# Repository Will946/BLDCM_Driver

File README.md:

# BLDC Motor Controller

> [!NOTE]
> This project is currently in active development. Features and documentation are subject to change.

## Table of Contents
- [Project Overview](#project-overview)
- [Electronics](#electronics)
  - [MCU PCB (Top Board)](#mcu-pcb-top-board)
  - [Power PCB (Bottom Board)](#power-pcb-bottom-board)
  - [Complete Stack-Up](#complete-stack-up)
- [Results](#results)

---

## Project Overview

This project aims to develop a **high-precision Brushless DC (BLDC) motor controller** from scratch, covering both hardware and firmware aspects. The controller is designed for advanced motor control applications, leveraging a powerful STM32 microcontroller, a dedicated motor driver IC, and comprehensive sensing capabilities for precise operation and rotor position estimation.

The core of the system is a custom two-board stack: an MCU board housing the main control logic and a power board managing motor drive and sensing. The two boards connect through a Molex board-to-board stack connector, keeping the whole assembly compact enough to sit directly behind the motor.

<div align="center">
  
  &nbsp;&nbsp;
  
</div>

---

## Electronics

The electronics consist of two interconnected custom-designed Printed Circuit Boards (PCBs), designed using **KiCad**. Both boards are **4-layer, circular designs** sized to fit inside the motor housing, and stack together through a **Molex board-to-board connector** that carries power, control signals, and communication lines between them.

### MCU PCB (Top Board)

The top PCB is the brain of the controller. It runs the control loop, reads all of the position/motion sensors, and exposes the debug and status interfaces a developer needs while bringing the system up.

<div align="center">
  
  &nbsp;&nbsp;
  
</div>

**How it works:**
- The **STM32F4 microcontroller** sits at the center of the board and runs the motor control algorithm (trapezoidal or FOC) in a fast timer-driven loop, reading sensor data and updating the PWM duty cycles sent down to the power board on every cycle.
- The **AS5048A** magnetic angle encoder reads the rotor's absolute position with 14-bit resolution off a magnet mounted on the motor shaft. This gives the controller true rotor position for commutation, rather than relying on back-EMF sensing, which matters a lot at low speed and standstill.
- The **ISM330DHCX IMU** adds acceleration and angular velocity data from the board itself, which is useful for detecting external motion or vibration and for any application where the motor's own orientation/movement (not just the rotor's) needs to be tracked.
- An **SK6805 RGB LED ring** wraps around the board's edge and is driven per-LED to show system status (idle, running, fault, etc.) at a glance without needing a debugger attached.
- A **reset button** is broken out on the edge for quick resets during bring-up and testing.
- The top-side connector routes down to the power board through the Molex stack connector, carrying the PWM/gate signals, sensor feedback, and shared power rails between the two boards.

### Power PCB (Bottom Board)

The bottom PCB handles everything high-current: driving the motor phases, sensing voltage and current, and providing the external connectivity for power and communication.

<div align="center">
  
  &nbsp;&nbsp;
  
</div>

**How it works:**
- The **TMC6300** is a fully integrated 3-phase gate driver/MOSFET bridge. It takes the PWM commutation signals from the MCU board and switches the three motor phases directly — there's no separate discrete MOSFET stage, which keeps the board small enough to fit the round form factor.
- Three **INA240** current sense amplifiers measure the current on each motor phase in real time. This phase current feedback is what the FOC algorithm on the MCU board needs to run its current control loops (the Park/Clarke transforms depend on accurate, low-noise current readings).
- Four voltage sensing networks monitor the **DC bus voltage** plus all **three phase voltages** (after filtering), letting the firmware detect undervoltage/overvoltage conditions and, combined with the current sensing, estimate power delivered to the motor.
- The **TCAN1462** CAN FD transceiver lets multiple motor controllers be **daisy-chained together on a single CAN bus**, so a single host can address and command several motors (e.g. in a multi-joint robot) over one pair of wires.
- A **J-Link 14-pin SWD connector** breaks out the STM32's debug port for flashing and live debugging with a J-Link probe.
- A **USB-C connector** provides Full-Speed USB for data logging, host-side control, and can also be used to supply power to the board during bench testing.
- Two **4-pin Molex Micro-Lock Plus connectors** on the sides carry motor power and CAN out to the next board in the chain, using a locking, vibration-resistant connector rather than a bare header.

---

### Complete Stack-Up

The MCU and Power boards aren't independent — they're designed as a single functional unit that happens to be split across two PCBs, connected face-to-face by the Molex board-to-board connector so the whole stack fits behind the motor in a slim, cylindrical footprint.

- **Control signal path:** the STM32 on the MCU board computes the commutation state (trapezoidal or FOC) and outputs PWM/gate-control signals, which cross the stack connector down to the TMC6300 driver on the Power board. The TMC6300 does the actual high-current switching of the three motor phases.
- **Feedback path:** the Power board's three INA240 current sense amplifiers and four voltage sensing networks measure what's actually happening on the phases and DC bus, and that analog/digital feedback travels back up across the same connector to the STM32's ADCs, closing the current and voltage control loops each control cycle.
- **Position feedback stays local:** the AS5048A encoder and ISM330DHCX IMU are both on the MCU board, next to the STM32, so rotor position and motion data never have to cross the board-to-board connector — only the commutation output and phase feedback do.
- **Shared power rails:** the Power board is where motor power and USB-C power come in; the regulated logic rails needed by the MCU board are distributed up through the stack connector, so only one board needs external power wiring.
- **External I/O lives on the Power board:** USB-C, the CAN bus (for daisy-chaining multiple controllers), and the J-Link SWD debug header are all broken out on the Power board's edge, since that's the board facing the outside of the housing — while status (LED ring) and reset live on the MCU board, which faces the user/inspection side.

In short: the Power board is the "muscle and senses" (driving the motor, measuring current/voltage, talking to the outside world), and the MCU board is the "brain" (running the control algorithm and tracking rotor position) — the stack connector is what ties the two into one closed-loop controller.

---

## Results

Below are some pictures/video taken during development, showing the bench setup used to bring up the firmware (reading out PWM and phase signals on the oscilloscope) and a cross-section render of the motor housing. The controller design and calibration procedures will be explained in depth in the future :)

<div align="center">

**[▶ Watch the test video](BLDCTest.mp4)**

</div>

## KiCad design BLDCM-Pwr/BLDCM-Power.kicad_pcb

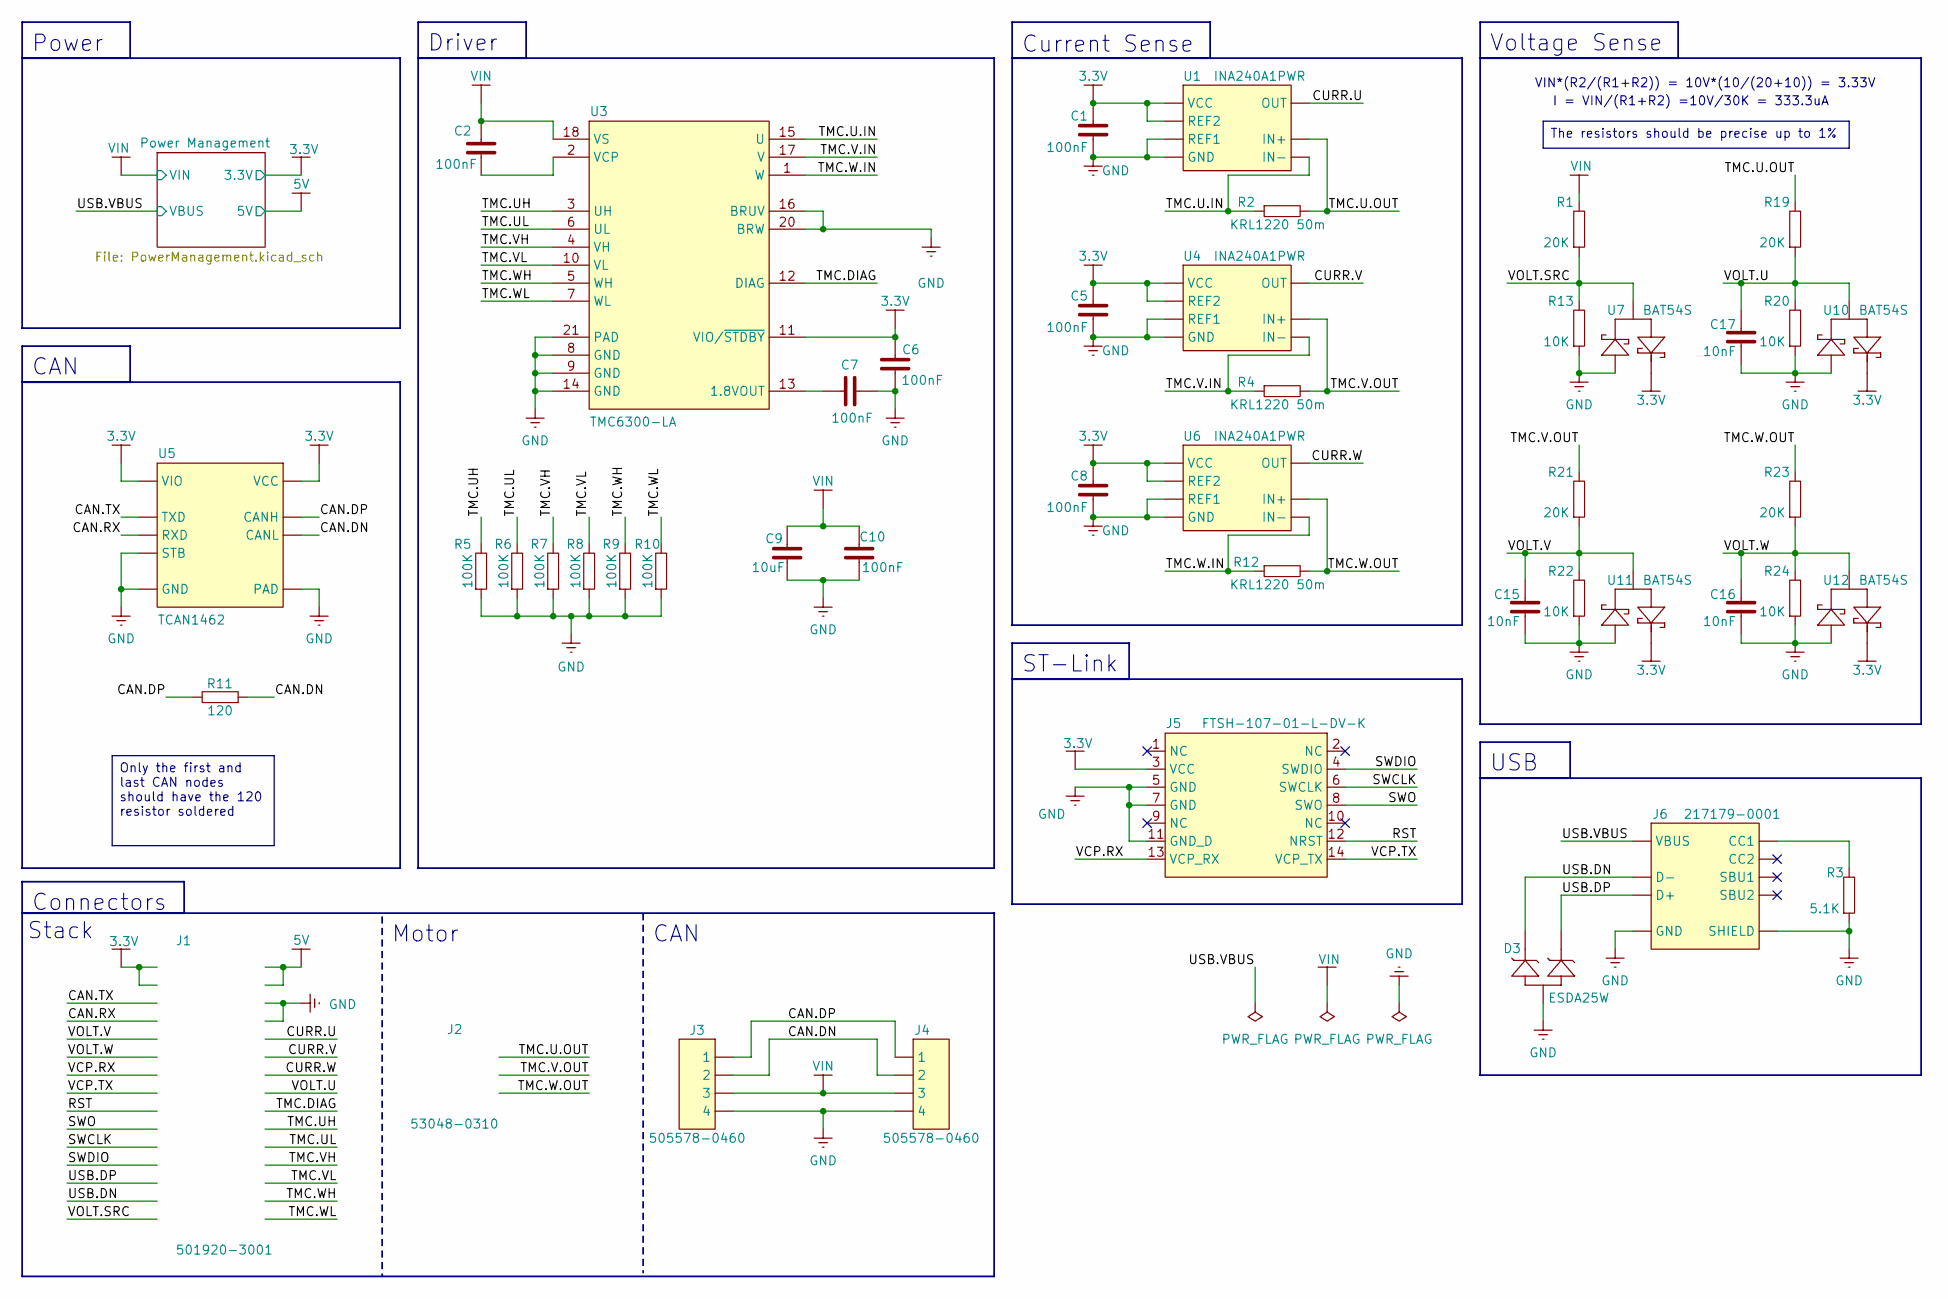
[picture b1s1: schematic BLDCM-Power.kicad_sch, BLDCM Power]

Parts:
C1, C2, C5, C6, C7, C8, C10: 100nF; C_0402
C9: 10uF; C_0402
C15, C16, C17: 10nF; C_0402
D3: ESDA25W; SOT-323
J1: 501920-3001
J2: 53048-0310
J3, J4: 505578-0460
J5: FTSH-107-01-L-DV-K; FTSH-107-01-L-DV-K-TR
J6: 217179-0001
R1, R19, R21, R23: 20K; R_0402
R2, R4, R12: KRL1220 50m; KRL1220
R3: 5.1K; R_0402
R5, R6, R7, R8, R9, R10: 100K; R_0402
R11: 120; R_0402
R13, R20, R22, R24: 10K; R_0402
U1, U4, U6: INA240A1PWR; TSSOP-8
U3: TMC6300-LA; QFN-20
U5: TCAN1462; VSON-8
U7, U10, U11, U12: BAT54S; SOT-23

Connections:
3.3V: C1.1, C5.1, C6.2, C8.1, J1.1, J1.3, J5.3 (VCC), U1.5 (VCC), U1.6 (REF2), U3.11 (VIO/~STDBY), U4.5 (VCC), U4.6 (REF2), U5.3 (VCC), U5.5 (VIO), U6.5 (VCC), U6.6 (REF2), U7.2, U10.2, U11.2, U12.2; also elsewhere on the board
5V: J1.2, J1.4; also elsewhere on the board
/CAN.DN: J3.2, J4.2, R11.1, U5.6 (CANL)
/CAN.DP: J3.1, J4.1, R11.2, U5.7 (CANH)
/CAN.RX: J1.7, U5.4 (RXD)
/CAN.TX: J1.5, U5.1 (TXD)
/CURR.U: J1.10, U1.8 (OUT)
/CURR.V: J1.12, U4.8 (OUT)
/CURR.W: J1.14, U6.8 (OUT)
/RST: J1.17, J5.12 (NRST)
/SWCLK: J1.21, J5.6 (SWCLK)
/SWDIO: J1.23, J5.4 (SWDIO)
/SWO: J1.19, J5.8 (SWO)
/TMC.DIAG: J1.18, U3.12 (DIAG)
/TMC.U.IN: R2.1, U1.3 (IN-), U3.15 (U)
/TMC.U.OUT: J2.1, R2.2, R19.2, U1.2 (IN+)
/TMC.UH: J1.20, R5.2, U3.3 (UH)
/TMC.UL: J1.22, R6.2, U3.6 (UL)
/TMC.V.IN: R4.1, U3.17 (V), U4.3 (IN-)
/TMC.V.OUT: J2.2, R4.2, R21.2, U4.2 (IN+)
/TMC.VH: J1.24, R7.2, U3.4 (VH)
/TMC.VL: J1.26, R8.2, U3.10 (VL)
/TMC.W.IN: R12.1, U3.1 (W), U6.3 (IN-)
/TMC.W.OUT: J2.3, R12.2, R23.2, U6.2 (IN+)
/TMC.WH: J1.28, R9.2, U3.5 (WH)
/TMC.WL: J1.30, R10.2, U3.7 (WL)
/USB.DN: D3.1, J1.27, J6.A7 (D-), J6.B7 (D-2)
/USB.DP: D3.2, J1.25, J6.A6 (D+), J6.B6 (D+2)
/VCP.RX: J1.13, J5.13 (VCP_RX)
/VCP.TX: J1.15, J5.14 (VCP_TX)
/VOLT.SRC: J1.29, R1.1, R13.2, U7.3
/VOLT.U: C17.2, J1.16, R19.1, R20.2, U10.3
/VOLT.V: C15.2, J1.9, R21.1, R22.2, U11.3
/VOLT.W: C16.2, J1.11, R23.1, R24.2, U12.3
GND: C1.2, C5.2, C6.1, C7.1, C8.2, C9.1, C10.1, C15.1, C16.1, C17.1, D3.3, J1.6, J1.8, J3.4, J4.4, J5.5 (GND), J5.7 (GND), J5.11 (GND_D), J6.A1_B12 (GND), J6.B1_A12 (GND), J6.SH1 (SHIELD), J6.SH2 (SHIELD), J6.SH3 (SHIELD), J6.SH4 (SHIELD), R3.1, R5.1, R6.1, R7.1, R8.1, R9.1, R10.1, R13.1, R20.1, R22.1, R24.1, U1.4 (GND), U1.7 (REF1), U3.8 (GND), U3.9 (GND), U3.14 (GND), U3.16 (BRUV), U3.20 (BRW), U3.21 (PAD), U4.4 (GND), U4.7 (REF1), U5.2 (GND), U5.8 (STB), U5.PAD, U6.4 (GND), U6.7 (REF1), U7.1, U10.1, U11.1, U12.1; also elsewhere on the board
unnamed: J6.A5 (CC1), R3.2
unnamed: C7.2, U3.13 (1.8VOUT)
unnamed: C2.1, U3.2 (VCP)
VBUS: J6.A4_B9 (VBUS), J6.B4_A9 (VBUS); also elsewhere on the board
VIN: C2.2, C9.2, C10.2, J3.3, J4.3, R1.2, U3.18 (VS); also elsewhere on the board

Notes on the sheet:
ST-Link
I = VIN/(R1+R2) =10V/30K = 333.3uA
Driver
Stack
Power
CAN
VIN*(R2/(R1+R2)) = 10V*(10/(20+10)) = 3.33V
Motor
Voltage Sense
USB
Connectors
Current Sense
The resistors should be precise up to 1%
Only the first and last CAN nodes should have the 120 resistor soldered

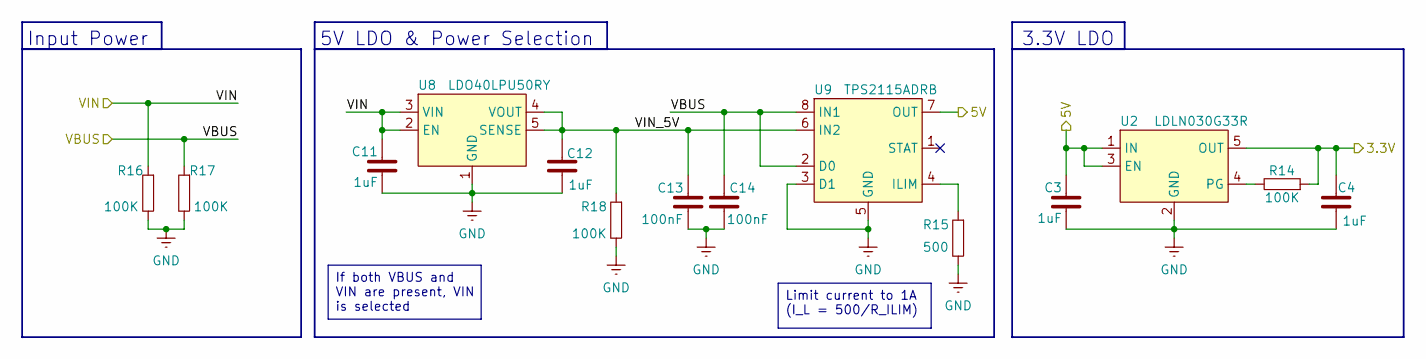
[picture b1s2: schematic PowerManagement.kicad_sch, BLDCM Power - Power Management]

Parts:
C3, C4, C11, C12: 1uF; C_0402
C13, C14: 100nF; C_0402
R14, R16, R17, R18: 100K; R_0402
R15: 500; R_0402
U2: LDLN030G33R; TSOT-23-5
U8: LDO40LPU50RY; DFN-6-3x3
U9: TPS2115ADRB; VSON-8

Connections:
3.3V: C4.2, R14.1, U2.5 (OUT); also elsewhere on the board
5V: C3.2, U2.1 (IN), U2.3 (EN), U9.7 (OUT); also elsewhere on the board
/Power Management/VIN_5V: C12.2, C13.1, R18.1, U8.4 (VOUT), U8.5 (SENSE), U9.6 (IN2)
GND: C3.1, C4.1, C11.1, C12.1, C13.2, C14.2, R15.2, R16.2, R17.2, R18.2, U2.2 (GND), U8.1 (GND), U8.PAD, U9.3 (D1), U9.5 (GND), U9.PAD; also elsewhere on the board
unnamed: R14.2, U2.4 (PG)
unnamed: R15.1, U9.4 (ILIM)
VBUS: C14.1, R17.1, U9.2 (D0), U9.8 (IN1); also elsewhere on the board
VIN: C11.2, R16.1, U8.2 (EN), U8.3 (VIN); also elsewhere on the board

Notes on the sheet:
Input Power
3.3V LDO
5V LDO & Power Selection
Limit current to 1A (I_L = 500/R_ILIM)
If both VBUS and VIN are present, VIN is selected

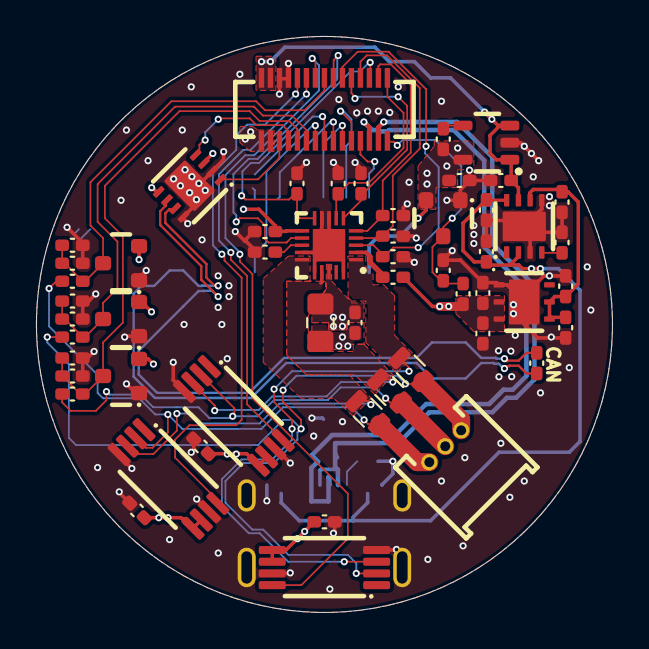
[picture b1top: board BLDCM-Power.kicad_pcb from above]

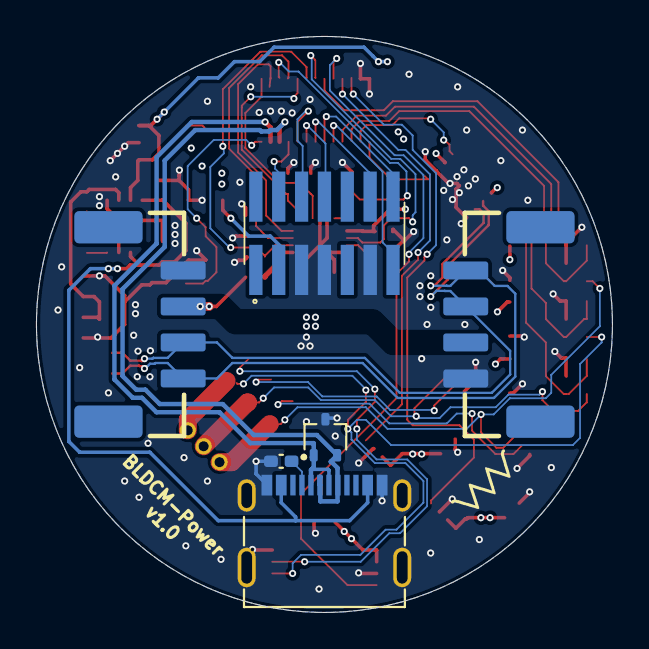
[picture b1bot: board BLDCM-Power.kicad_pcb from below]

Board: 4 copper layers, 32.0 x 32.0 mm, 60 parts (6 on the bottom side), 43 nets.

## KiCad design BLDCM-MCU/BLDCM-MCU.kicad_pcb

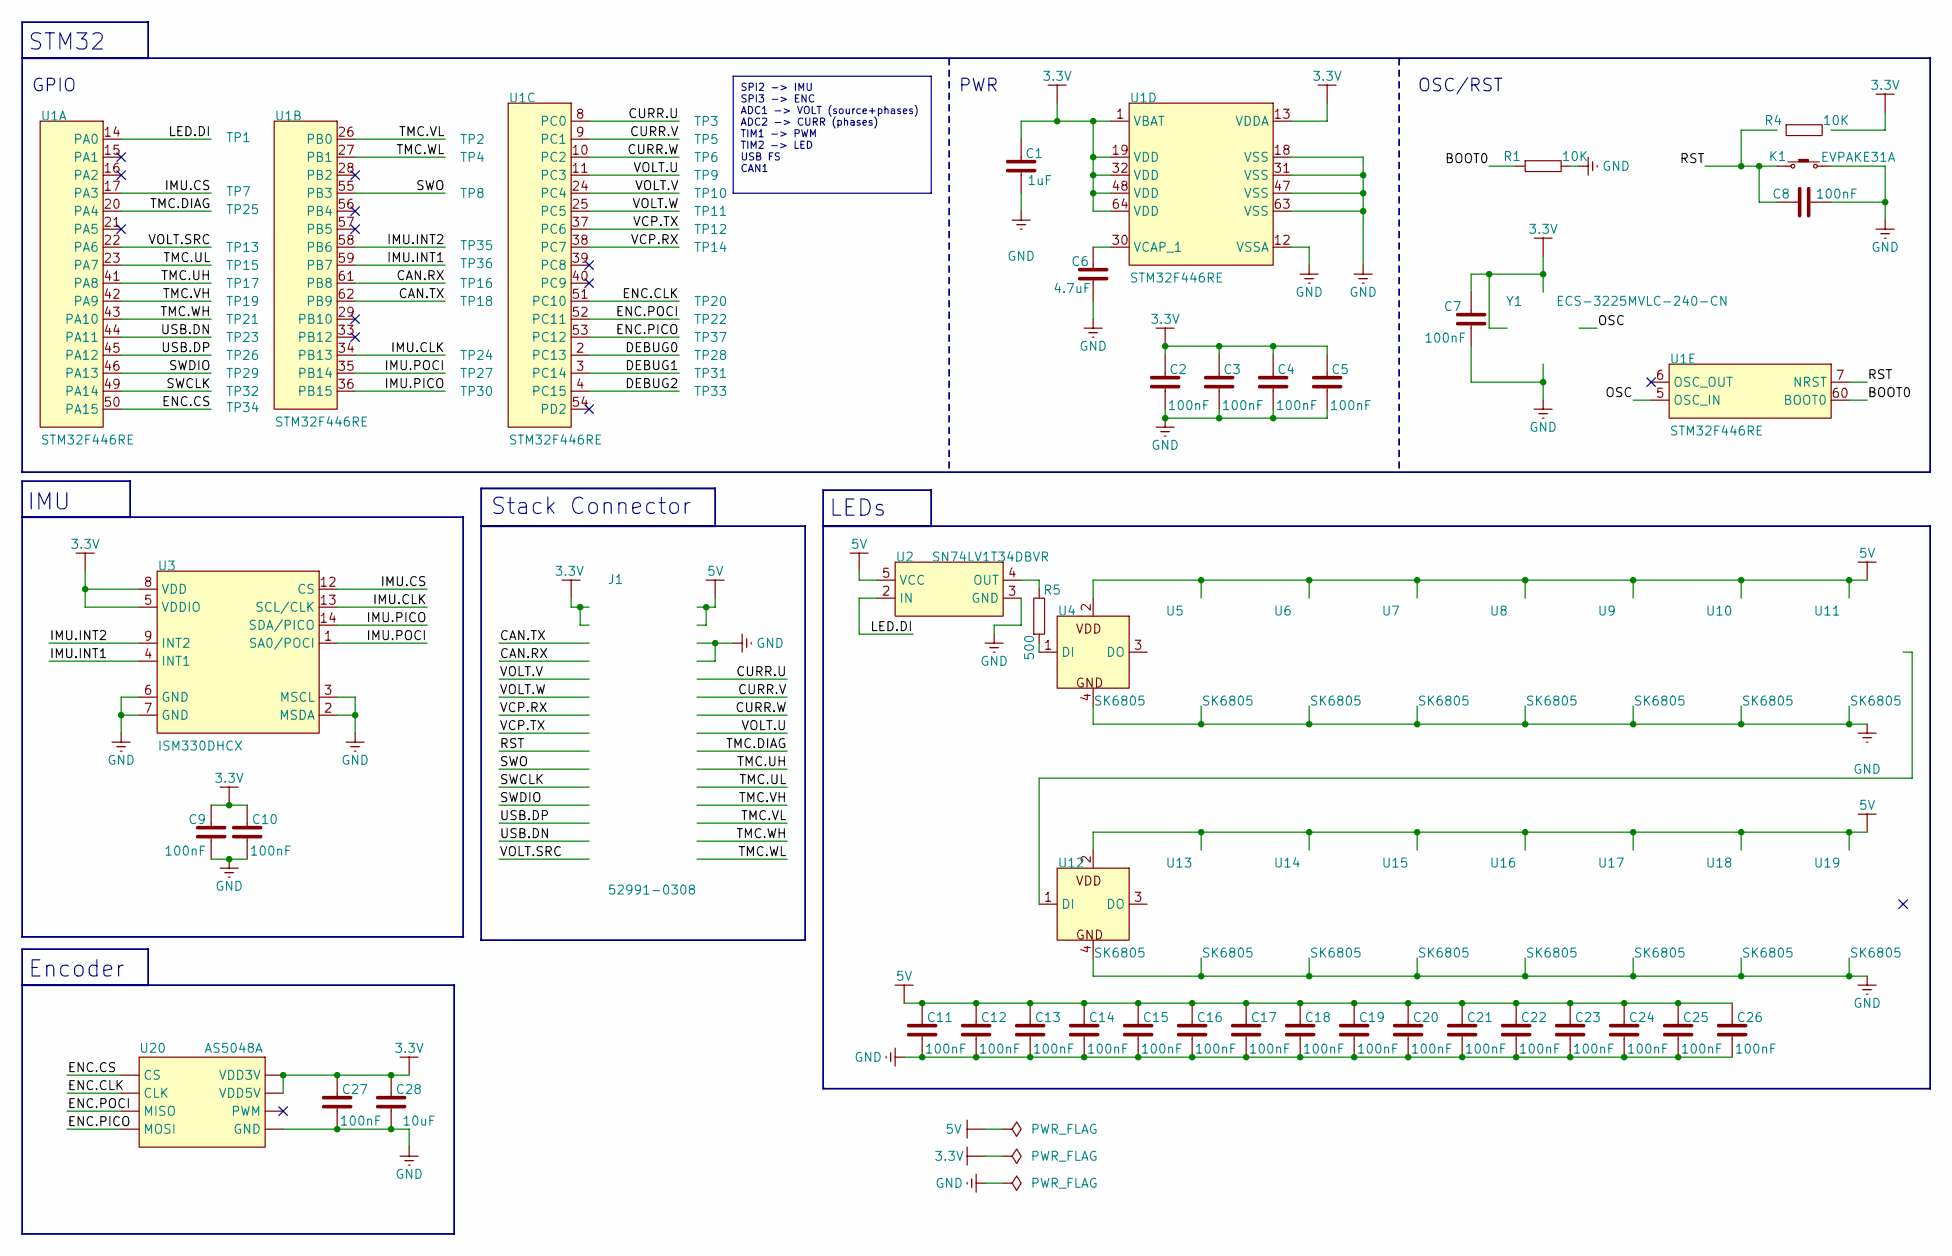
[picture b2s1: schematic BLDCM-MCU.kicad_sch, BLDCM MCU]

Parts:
C1: 1uF; C_0402
C2, C3, C4, C5, C7, C8, C9, C10, C11, C12, C13, C14, C15, C16, C17, C18, C19, C20, C21, C22, C23, C24, C25, C26, C27: 100nF; C_0402
C6: 4.7uF; C_0402
C28: 10uF; C_0402
J1: 52991-0308
K1: EVPAKE31A
R1, R4: 10K; R_0402
R5: 500; R_0402
TP1, TP2, TP3, TP4, TP5, TP6, TP7, TP8, TP9, TP10, TP11, TP12, TP13, TP14, TP15, TP16, TP17, TP18, TP19, TP20, TP21, TP22, TP23, TP24, TP25, TP26, TP27, TP28, TP29, TP30, TP31, TP32, TP33, TP34, TP35, TP36, TP37: Test point 0.5mm; TP_0.5mm
U1: STM32F446RE; LQFP64
U2: SN74LV1T34DBVR; SOT-23-5
U3: ISM330DHCX; LGA-14L
U4, U5, U6, U7, U8, U9, U10, U11, U12, U13, U14, U15, U16, U17, U18, U19: SK6805; LED-1515
U20: AS5048A; TSSOP-14
Y1: ECS-3225MVLC-240-CN; Crystal_3225

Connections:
3.3V: C1.2, C2.2, C3.2, C4.2, C5.2, C7.2, C9.2, C10.2, C27.2, C28.2, J1.1, J1.3, R4.2, U1.1 (VBAT), U1.13 (VDDA), U1.19 (VDD), U1.32 (VDD), U1.48 (VDD), U1.64 (VDD), U3.5 (VDDIO), U3.8 (VDD), U20.11 (VDD5V), U20.12 (VDD3V), Y1.1, Y1.4
5V: C11.2, C12.2, C13.2, C14.2, C15.2, C16.2, C17.2, C18.2, C19.2, C20.2, C21.2, C22.2, C23.2, C24.2, C25.2, C26.2, J1.2, J1.4, U2.5 (VCC), U4.2 (VDD), U5.2 (VDD), U6.2 (VDD), U7.2 (VDD), U8.2 (VDD), U9.2 (VDD), U10.2 (VDD), U11.2 (VDD), U12.2 (VDD), U13.2 (VDD), U14.2 (VDD), U15.2 (VDD), U16.2 (VDD), U17.2 (VDD), U18.2 (VDD), U19.2 (VDD)
/BOOT0: R1.1, U1.60 (BOOT0)
/CAN.RX: J1.7, TP16.1, U1.61 (PB8)
/CAN.TX: J1.5, TP18.1, U1.62 (PB9)
/CURR.U: J1.10, TP3.1, U1.8 (PC0)
/CURR.V: J1.12, TP5.1, U1.9 (PC1)
/CURR.W: J1.14, TP6.1, U1.10 (PC2)
/DEBUG0: TP28.1, U1.2 (PC13)
/DEBUG1: TP31.1, U1.3 (PC14)
/DEBUG2: TP33.1, U1.4 (PC15)
/ENC.CLK: TP20.1, U1.51 (PC10), U20.2 (CLK)
/ENC.CS: TP34.1, U1.50 (PA15), U20.1 (CS)
/ENC.PICO: TP37.1, U1.53 (PC12), U20.4 (MOSI)
/ENC.POCI: TP22.1, U1.52 (PC11), U20.3 (MISO)
/IMU.CLK: TP24.1, U1.34 (PB13), U3.13 (SCL/CLK)
/IMU.CS: TP7.1, U1.17 (PA3), U3.12 (CS)
/IMU.INT1: TP36.1, U1.59 (PB7), U3.4 (INT1)
/IMU.INT2: TP35.1, U1.58 (PB6), U3.9 (INT2)
/IMU.PICO: TP30.1, U1.36 (PB15), U3.14 (SDA/PICO)
/IMU.POCI: TP27.1, U1.35 (PB14), U3.1 (SA0/POCI)
/LED.DI: TP1.1, U1.14 (PA0), U2.2 (IN)
/OSC: U1.5 (OSC_IN), Y1.3
/RST: C8.2, J1.17, K1.1, R4.1, U1.7 (NRST)
/SWCLK: J1.21, TP32.1, U1.49 (PA14)
/SWDIO: J1.23, TP29.1, U1.46 (PA13)
/SWO: J1.19, TP8.1, U1.55 (PB3)
/TMC.DIAG: J1.18, TP25.1, U1.20 (PA4)
/TMC.UH: J1.20, TP17.1, U1.41 (PA8)
/TMC.UL: J1.22, TP15.1, U1.23 (PA7)
/TMC.VH: J1.24, TP19.1, U1.42 (PA9)
/TMC.VL: J1.26, TP2.1, U1.26 (PB0)
/TMC.WH: J1.28, TP21.1, U1.43 (PA10)
/TMC.WL: J1.30, TP4.1, U1.27 (PB1)
/USB.DN: J1.27, TP23.1, U1.44 (PA11)
/USB.DP: J1.25, TP26.1, U1.45 (PA12)
/VCP.RX: J1.13, TP14.1, U1.38 (PC7)
/VCP.TX: J1.15, TP12.1, U1.37 (PC6)
/VOLT.SRC: J1.29, TP13.1, U1.22 (PA6)
/VOLT.U: J1.16, TP9.1, U1.11 (PC3)
/VOLT.V: J1.9, TP10.1, U1.24 (PC4)
/VOLT.W: J1.11, TP11.1, U1.25 (PC5)
GND: C1.1, C2.1, C3.1, C4.1, C5.1, C6.1, C7.1, C8.1, C9.1, C10.1, C11.1, C12.1, C13.1, C14.1, C15.1, C16.1, C17.1, C18.1, C19.1, C20.1, C21.1, C22.1, C23.1, C24.1, C25.1, C26.1, C27.1, C28.1, J1.6, J1.8, K1.2, R1.2, U1.12 (VSSA), U1.18 (VSS), U1.31 (VSS), U1.47 (VSS), U1.63 (VSS), U2.3 (GND), U3.2 (MSDA), U3.3 (MSCL), U3.6 (GND), U3.7 (GND), U4.4 (GND), U5.4 (GND), U6.4 (GND), U7.4 (GND), U8.4 (GND), U9.4 (GND), U10.4 (GND), U11.4 (GND), U12.4 (GND), U13.4 (GND), U14.4 (GND), U15.4 (GND), U16.4 (GND), U17.4 (GND), U18.4 (GND), U19.4 (GND), U20.13 (GND), Y1.2
unnamed: C6.2, U1.30 (VCAP_1)
unnamed: R5.2, U2.4 (OUT)
unnamed: R5.1, U4.1 (DI)
unnamed: U4.3 (DO), U5.1 (DI)
unnamed: U5.3 (DO), U6.1 (DI)
unnamed: U6.3 (DO), U7.1 (DI)
unnamed: U7.3 (DO), U8.1 (DI)
unnamed: U8.3 (DO), U9.1 (DI)
unnamed: U9.3 (DO), U10.1 (DI)
unnamed: U10.3 (DO), U11.1 (DI)
unnamed: U11.3 (DO), U12.1 (DI)
unnamed: U12.3 (DO), U13.1 (DI)
unnamed: U13.3 (DO), U14.1 (DI)
unnamed: U14.3 (DO), U15.1 (DI)
unnamed: U15.3 (DO), U16.1 (DI)
unnamed: U16.3 (DO), U17.1 (DI)
unnamed: U17.3 (DO), U18.1 (DI)
unnamed: U18.3 (DO), U19.1 (DI)

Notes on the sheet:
STM32
IMU
LEDs
Stack Connector
Encoder
OSC/RST
GPIO
PWR
SPI2 -> IMU SPI3 -> ENC ADC1 -> VOLT (source+phases) ADC2 -> CURR (phases) TIM1 -> PWM TIM2 -> LED USB FS CAN1

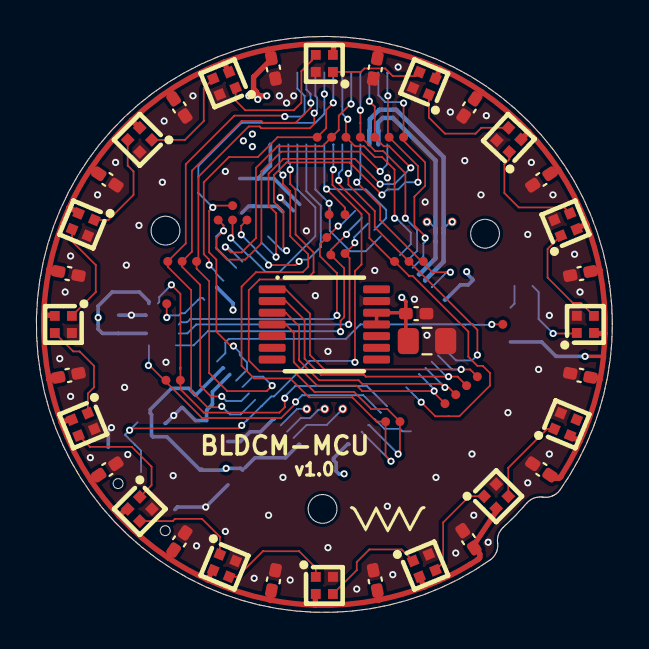
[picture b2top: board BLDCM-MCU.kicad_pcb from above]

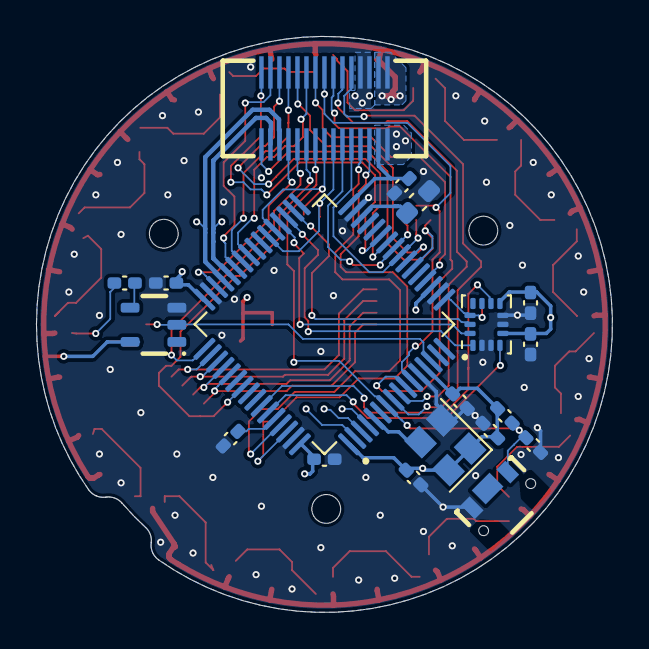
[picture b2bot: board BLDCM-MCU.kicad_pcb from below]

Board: 4 copper layers, 32.0 x 32.0 mm, 91 parts (19 on the bottom side), 61 nets.
